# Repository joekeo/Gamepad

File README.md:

# Gamepad
Mechanical left hand game-pad designed for gaming and productivity

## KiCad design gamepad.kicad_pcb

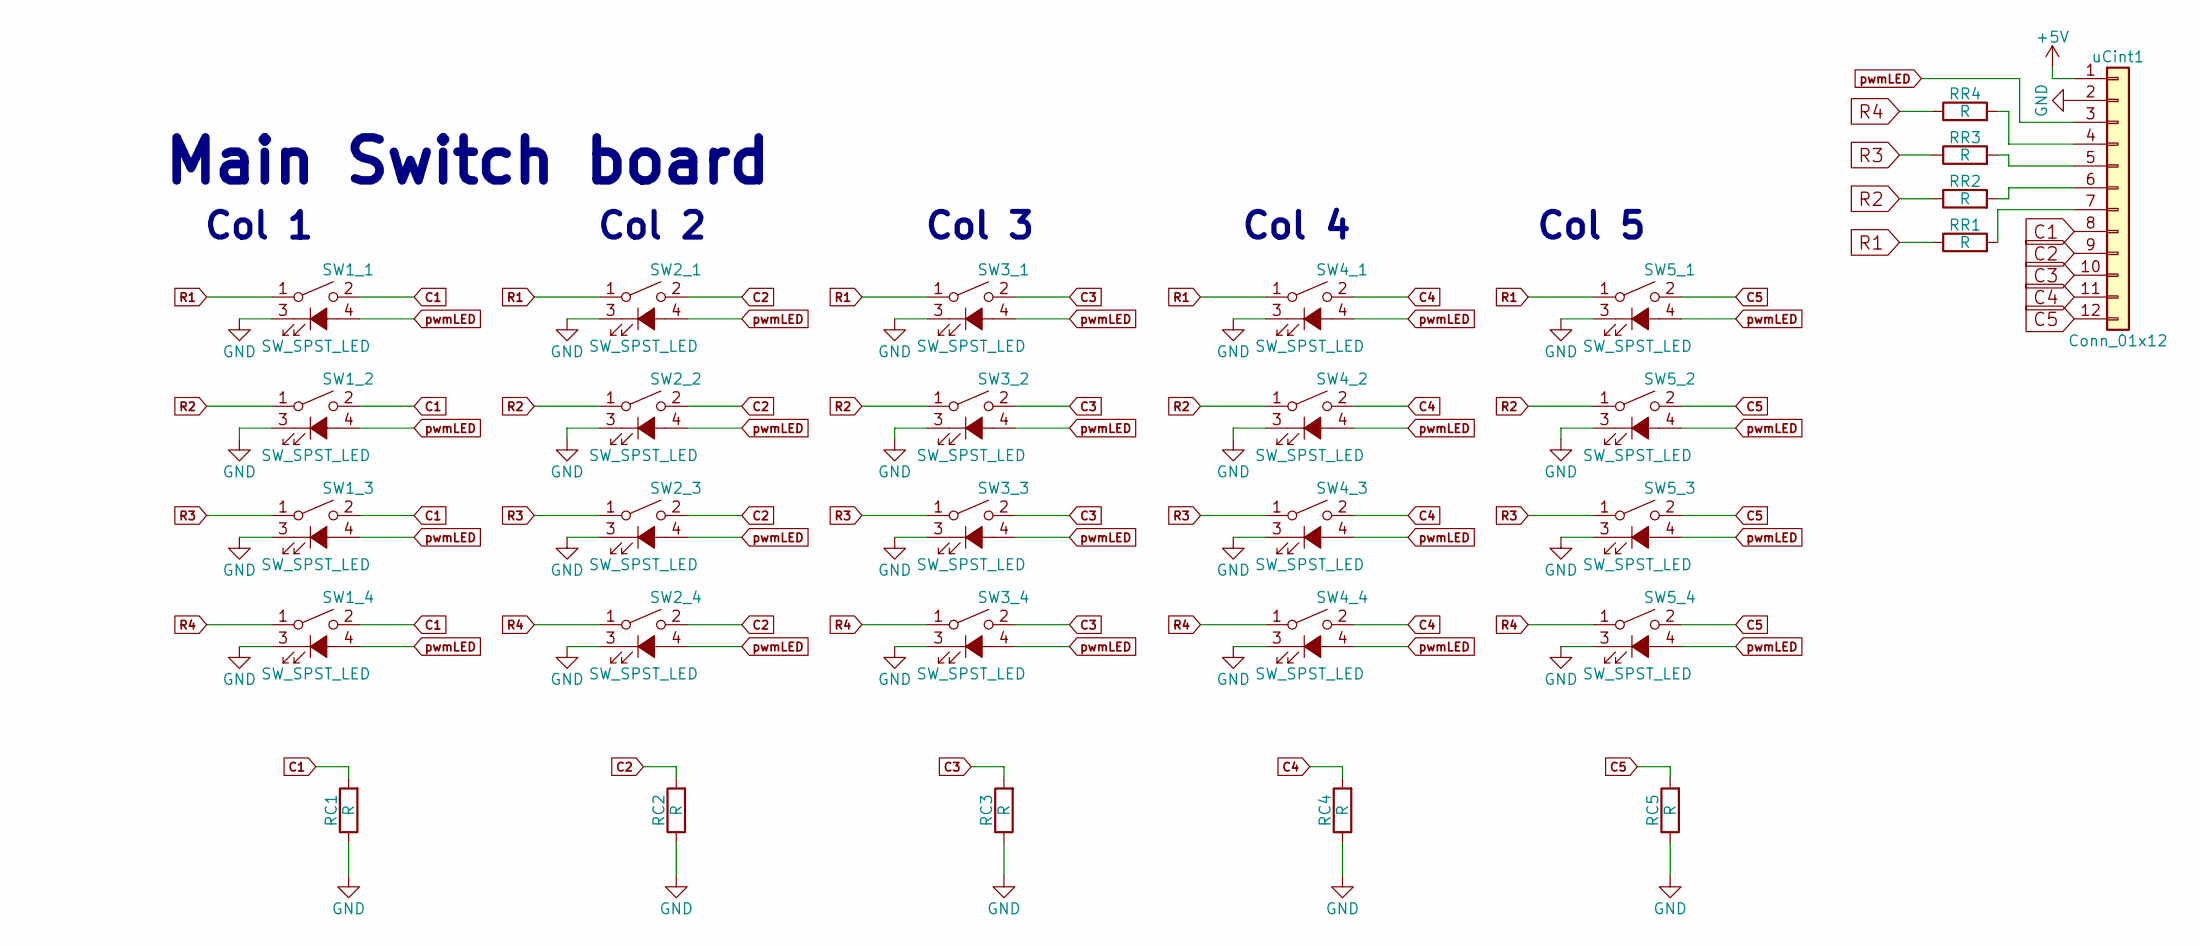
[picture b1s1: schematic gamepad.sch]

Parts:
RC1, RC2, RC3, RC4, RC5: R; R_Axial_DIN0207_L6.3mm_D2.5mm_P7.62mm_Horizontal
RR1, RR2, RR3, RR4: R; R_Axial_DIN0207_L6.3mm_D2.5mm_P7.62mm_Horizontal
SW1_1, SW1_2, SW1_3, SW1_4, SW2_1, SW2_2, SW2_3, SW2_4, SW3_1, SW3_2, SW3_3, SW3_4, SW4_1, SW4_2, SW4_3, SW4_4, SW5_1, SW5_2, SW5_3, SW5_4: SW_SPST_LED; CherryMX_PCB_DL
uCint1: Conn_01x12; Molex_Right_Angle_1.25_mm_12_Contacts

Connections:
+5V: uCint1.1
C1: RC1.2, SW1_1.2, SW1_2.2, SW1_3.2, SW1_4.2, uCint1.8
C2: RC2.2, SW2_1.2, SW2_2.2, SW2_3.2, SW2_4.2, uCint1.9
C3: RC3.2, SW3_1.2, SW3_2.2, SW3_3.2, SW3_4.2, uCint1.10
C4: RC4.2, SW4_1.2, SW4_2.2, SW4_3.2, SW4_4.2, uCint1.11
C5: RC5.2, SW5_1.2, SW5_2.2, SW5_3.2, SW5_4.2, uCint1.12
GND: RC1.1, RC2.1, RC3.1, RC4.1, RC5.1, SW1_1.3 (K), SW1_2.3 (K), SW1_3.3 (K), SW1_4.3 (K), SW2_1.3 (K), SW2_2.3 (K), SW2_3.3 (K), SW2_4.3 (K), SW3_1.3 (K), SW3_2.3 (K), SW3_3.3 (K), SW3_4.3 (K), SW4_1.3 (K), SW4_2.3 (K), SW4_3.3 (K), SW4_4.3 (K), SW5_1.3 (K), SW5_2.3 (K), SW5_3.3 (K), SW5_4.3 (K), uCint1.2
unnamed: RR1.2, uCint1.7
unnamed: RR2.2, uCint1.6
unnamed: RR3.2, uCint1.5
unnamed: RR4.2, uCint1.4
R1: RR1.1, SW1_1.1, SW2_1.1, SW3_1.1, SW4_1.1, SW5_1.1
R2: RR2.1, SW1_2.1, SW2_2.1, SW3_2.1, SW4_2.1, SW5_2.1
R3: RR3.1, SW1_3.1, SW2_3.1, SW3_3.1, SW4_3.1, SW5_3.1
R4: RR4.1, SW1_4.1, SW2_4.1, SW3_4.1, SW4_4.1, SW5_4.1
pwmLED: SW1_1.4 (A), SW1_2.4 (A), SW1_3.4 (A), SW1_4.4 (A), SW2_1.4 (A), SW2_2.4 (A), SW2_3.4 (A), SW2_4.4 (A), SW3_1.4 (A), SW3_2.4 (A), SW3_3.4 (A), SW3_4.4 (A), SW4_1.4 (A), SW4_2.4 (A), SW4_3.4 (A), SW4_4.4 (A), SW5_1.4 (A), SW5_2.4 (A), SW5_3.4 (A), SW5_4.4 (A), uCint1.3

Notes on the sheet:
Main Switch board
Col 1
Col 2
Col 3
Col 4
Col 5

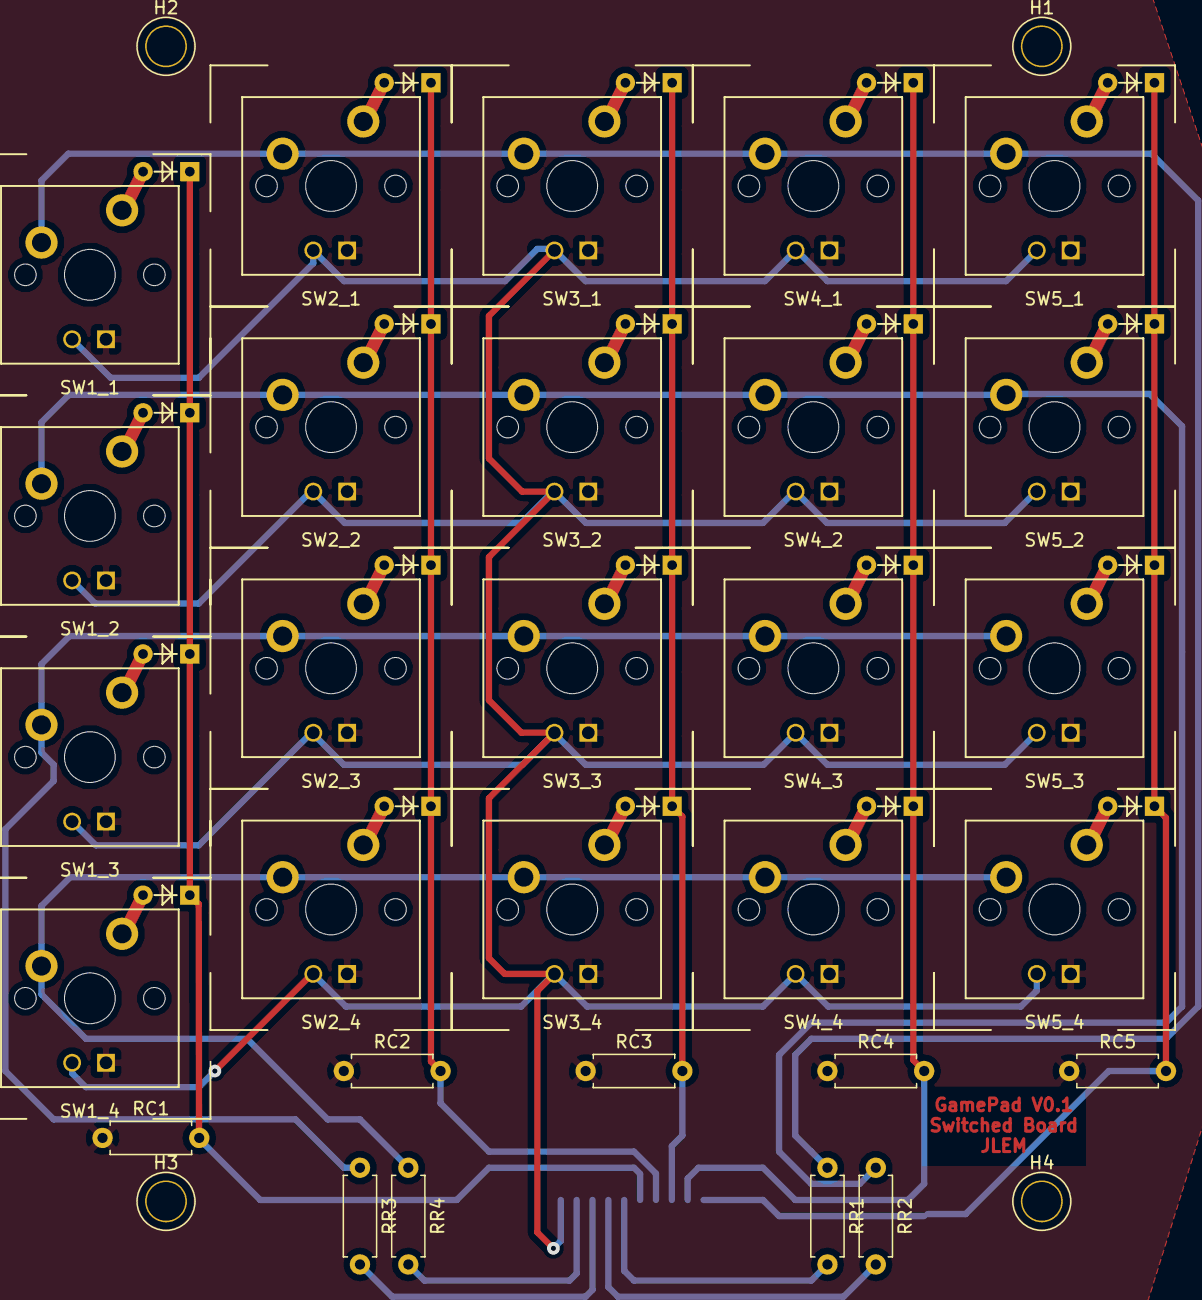
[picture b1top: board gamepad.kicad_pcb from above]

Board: 2 copper layers, 34 parts (1 on the bottom side), 15 nets.

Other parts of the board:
H1, H2, H3, H4: 3mm; 3mmHole

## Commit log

2017-11-06 Sch, board and some components
    This circuit design was done using Kicad. It it my first try at using this software, hope its nice.
2017-11-06 Modified the pcb-ready for first fab
    this is the first try of the pcb fab. It is still to be experted into altium, lets see how that goes :S
2017-11-06 changed some vias
2017-11-07 added the exported gerber and drill
2017-11-09 Added a folder with a 3d keycad CAD
2017-11-09 KeyCap STL for printing
2017-11-09 Modifications to the KeyCAP
2017-11-09 some modifications
2017-11-14 modified the units of the stl
2017-11-16 Aded an arduino leonardo USB interface
2017-11-17 updated the controls for the arduino micro pro connections
2017-11-21 Added profiles and profile switching
